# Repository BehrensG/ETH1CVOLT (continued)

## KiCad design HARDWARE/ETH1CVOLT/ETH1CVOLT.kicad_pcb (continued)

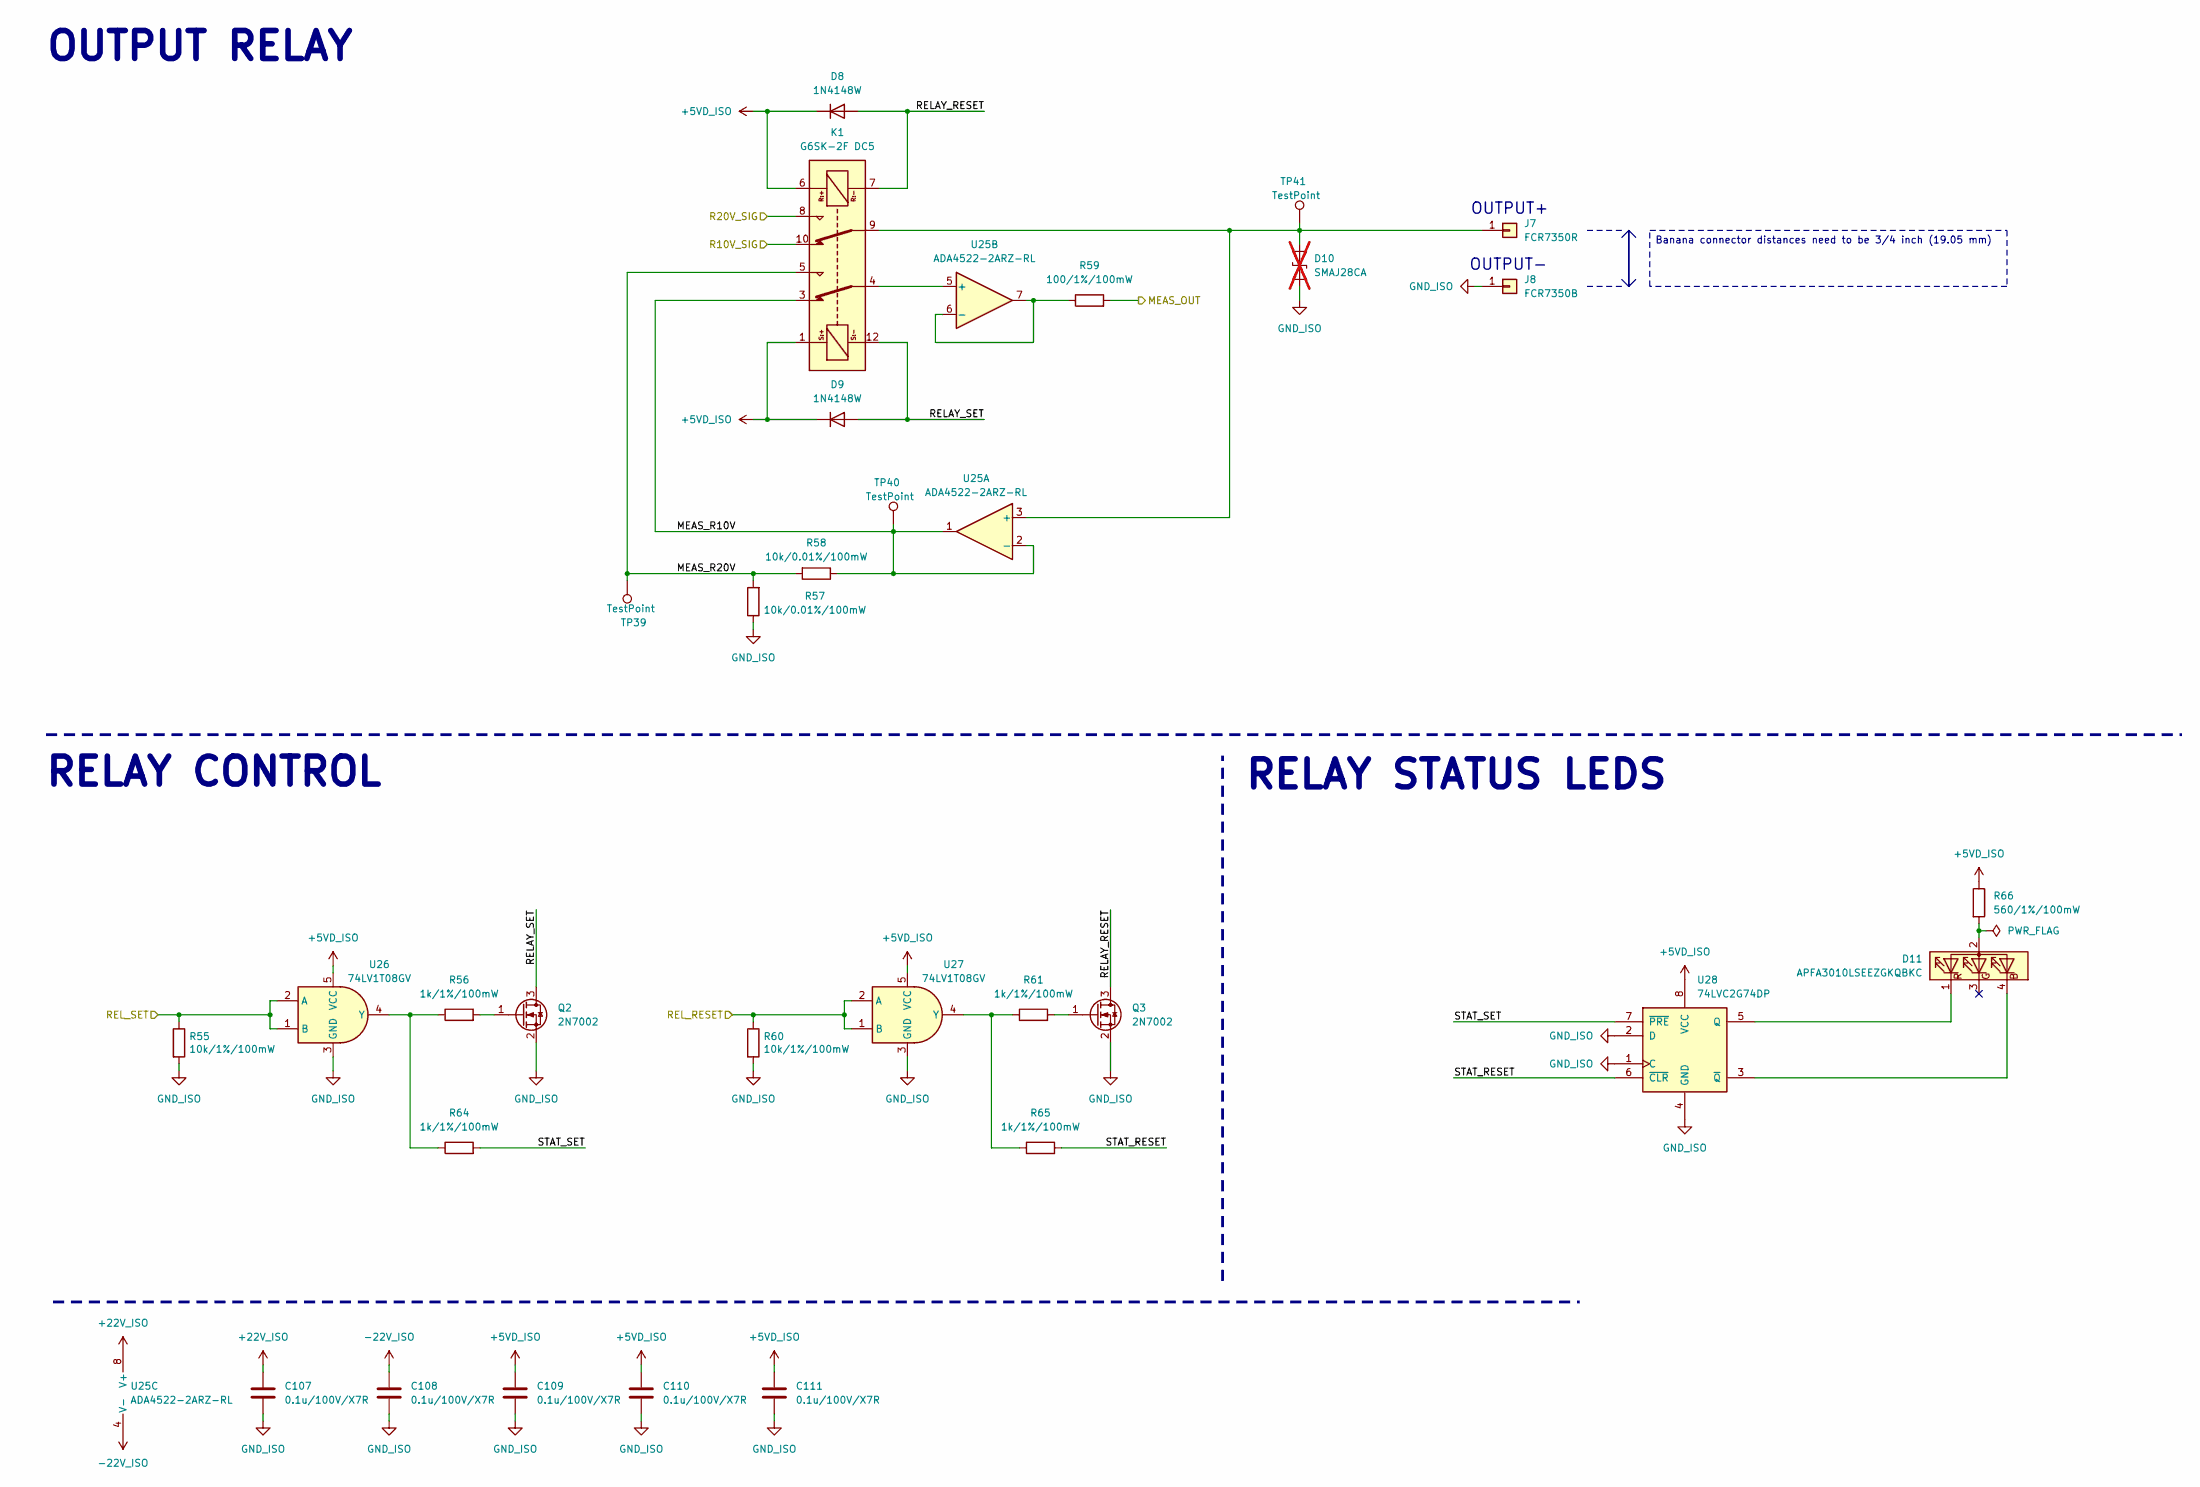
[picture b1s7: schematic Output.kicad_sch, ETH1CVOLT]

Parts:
C107, C108, C109, C110, C111: 0.1u/100V/X7R; C_0603_1608Metric_Pad1.08x0.95mm_HandSolder
D8, D9: 1N4148W; D_SOD-123
D10: SMAJ28CA; D_SMA; not fitted
D11: APFA3010LSEEZGKQBKC; LED_Kingbright_APFA3010_3x1.5mm_Horizontal
J7: FCR7350R; S16N-PC
J8: FCR7350B; S16N-PC
K1: G6SK-2F DC5; Relay_DPDT_Omron_G6SK-2F
Q2, Q3: 2N7002; SOT-23
R55, R60: 10k/1%/100mW; R_0603_1608Metric_Pad0.98x0.95mm_HandSolder
R56, R61, R64, R65: 1k/1%/100mW; R_0603_1608Metric_Pad0.98x0.95mm_HandSolder
R57, R58: 10k/0.01%/100mW; R_0603_1608Metric_Pad0.98x0.95mm_HandSolder
R59: 100/1%/100mW; R_0603_1608Metric_Pad0.98x0.95mm_HandSolder
R66: 560/1%/100mW; R_0603_1608Metric_Pad0.98x0.95mm_HandSolder
TP39, TP40, TP41: TestPoint; TestPoint_Pad_D1.5mm
U25: ADA4522-2ARZ-RL; SOIC-8_3.9x4.9mm_P1.27mm
U26, U27: 74LV1T08GV; SC-74A-5_1.55x2.9mm_P0.95mm
U28: 74LVC2G74DP; TSSOP-8_3x3mm_P0.65mm

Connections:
+5VD_ISO: C109.1, C110.1, C111.1, D8.1 (K), D9.1 (K), K1.1, K1.6, R66.1, U26.5 (VCC), U27.5 (VCC), U28.8 (VCC); also elsewhere on the board
+22V_ISO: C107.1, U25.8 (V+); also elsewhere on the board
-22V_ISO: C108.1, U25.4 (V-); also elsewhere on the board
/BLOCK DIAGRAM/ADC/MEAS_OUT: R59.2; also elsewhere on the board
/BLOCK DIAGRAM/ISO DIG/REL_RESET: R60.1, U27.1 (B), U27.2 (A); also elsewhere on the board
/BLOCK DIAGRAM/ISO DIG/REL_SET: R55.1, U26.1 (B), U26.2 (A); also elsewhere on the board
/BLOCK DIAGRAM/OUTPUT/MEAS_R10V: K1.3, R58.1, TP40.1 (1_1), U25.1, U25.2 (-)
/BLOCK DIAGRAM/OUTPUT/MEAS_R20V: K1.5, R57.2, R58.2, TP39.1 (1_1)
/BLOCK DIAGRAM/OUTPUT/R10V_SIG: K1.10; also elsewhere on the board
/BLOCK DIAGRAM/OUTPUT/R20V_SIG: K1.8; also elsewhere on the board
/BLOCK DIAGRAM/OUTPUT/RELAY_RESET: D8.2 (A), K1.7, Q3.3 (D)
/BLOCK DIAGRAM/OUTPUT/RELAY_SET: D9.2 (A), K1.12, Q2.3 (D)
/BLOCK DIAGRAM/OUTPUT/STAT_RESET: R65.2, U28.6 (~CLR)
/BLOCK DIAGRAM/OUTPUT/STAT_SET: R64.2, U28.7 (~PRE)
GND_ISO: C107.2, C108.2, C109.2, C110.2, C111.2, D10.1 (A1), J8.1 (Pin_1_1), Q2.2 (S), Q3.2 (S), R55.2, R57.1, R60.2, U26.3 (GND), U27.3 (GND), U28.1 (C), U28.2 (D), U28.4 (GND); also elsewhere on the board
unnamed: D10.2 (A2), J7.1 (Pin_1_1), K1.9, TP41.1 (1_1), U25.3 (+)
unnamed: D11.2 (A), R66.2
unnamed: D11.4 (B), U28.3 (~Q)
unnamed: D11.1 (R), U28.5 (Q)
unnamed: Q2.1 (G), R56.2
unnamed: Q3.1 (G), R61.2
unnamed: K1.4, U25.5 (+)
unnamed: R59.1, U25.6 (-), U25.7
unnamed: R56.1, R64.1, U26.4 (Y)
unnamed: R61.1, R65.1, U27.4 (Y)

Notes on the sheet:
RELAY CONTROL
OUTPUT-
OUTPUT+
OUTPUT RELAY
RELAY STATUS LEDS
Banana connector distances need to be 3/4 inch (19.05 mm)

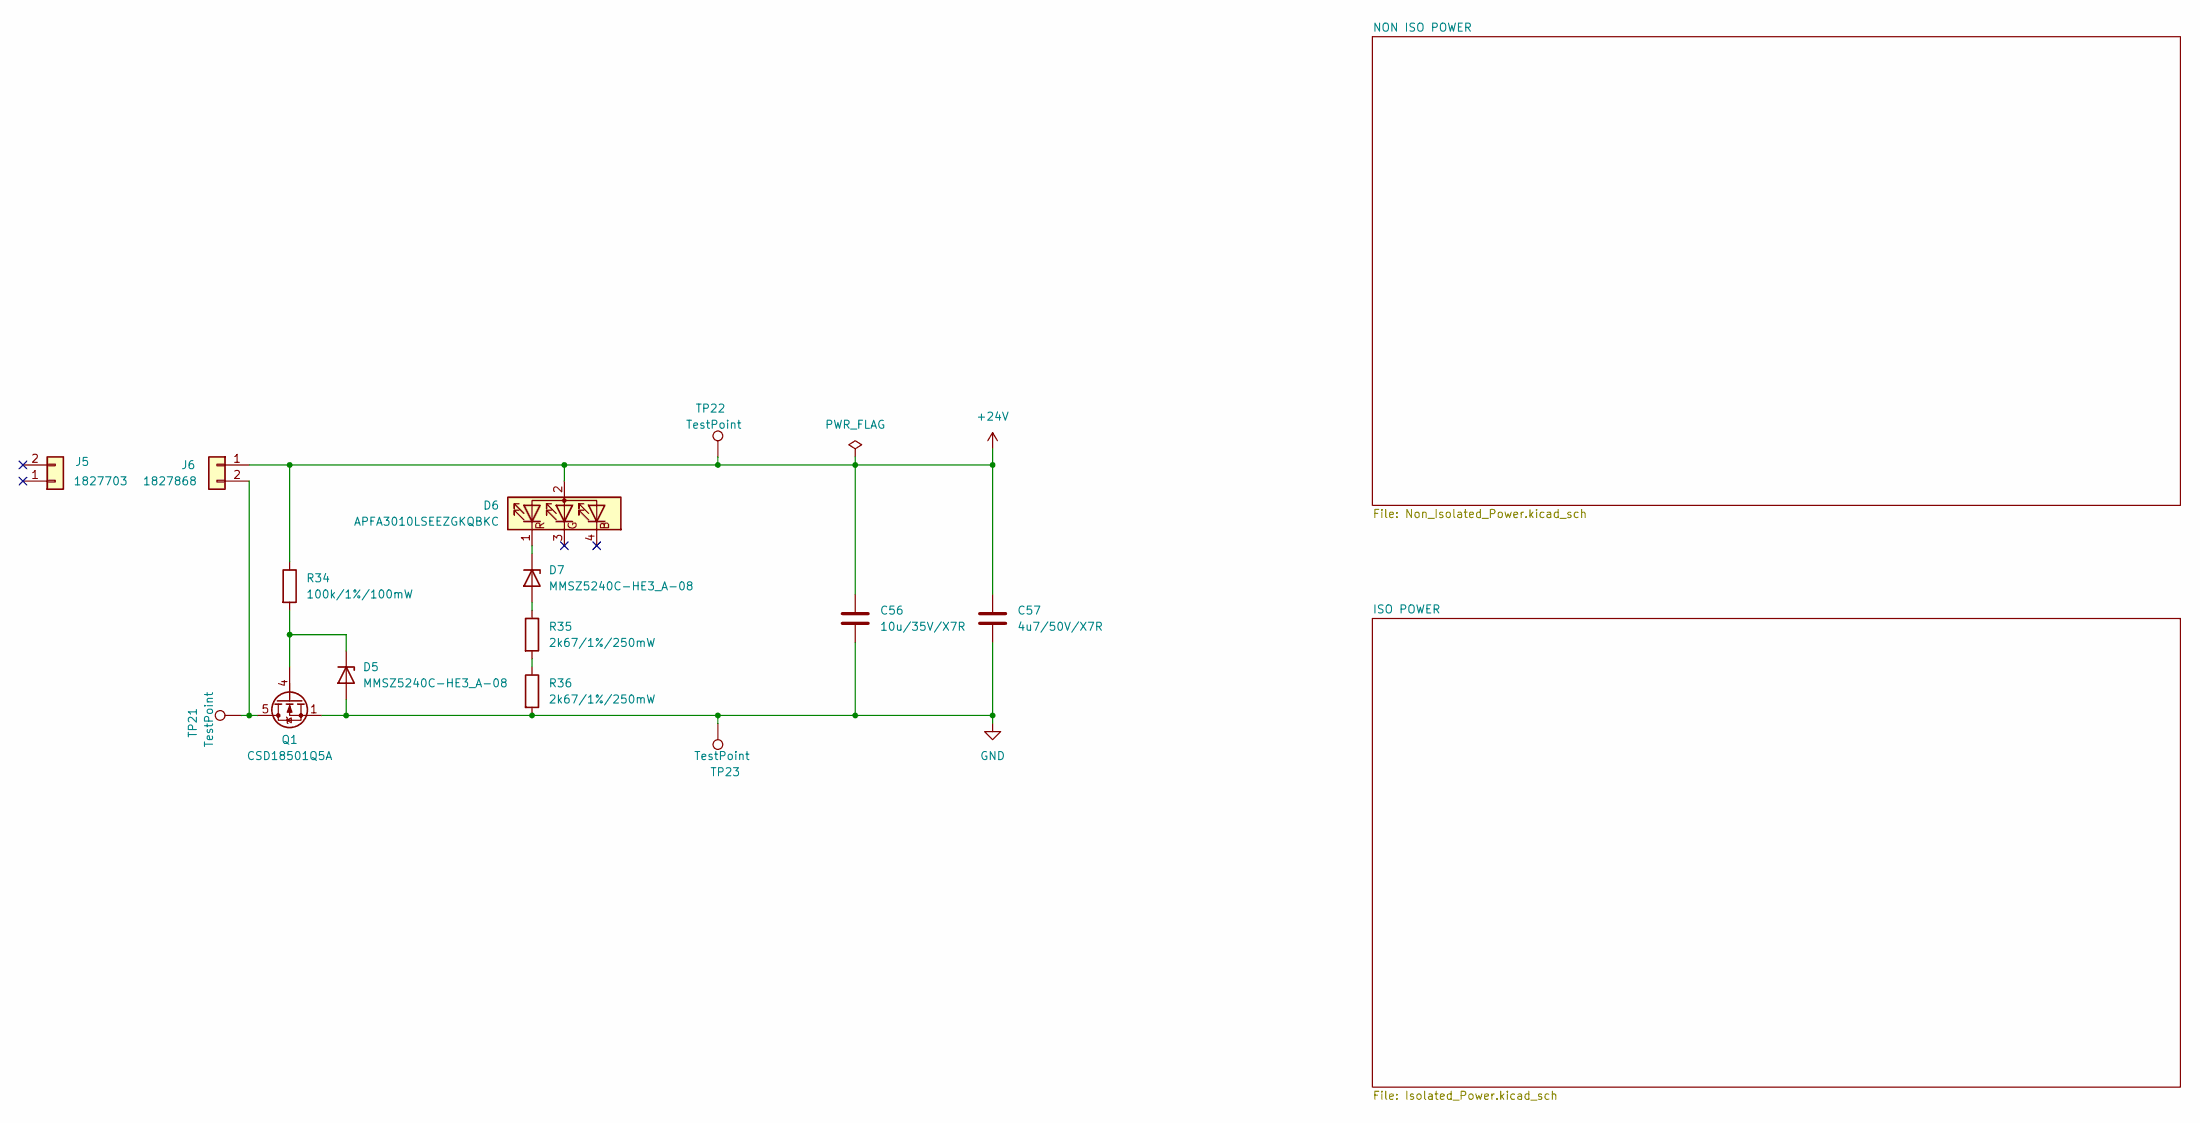
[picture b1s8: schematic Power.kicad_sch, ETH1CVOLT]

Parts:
C56: 10u/35V/X7R; C_1206_3216Metric_Pad1.33x1.80mm_HandSolder
C57: 4u7/50V/X7R; C_1206_3216Metric_Pad1.33x1.80mm_HandSolder
D5, D7: MMSZ5240C-HE3_A-08; D_SOD-123
D6: APFA3010LSEEZGKQBKC; LED_Kingbright_APFA3010_3x1.5mm_Horizontal
J5: 1827703
J6: 1827868; PhoenixContact_MC_1,5_2-GF-3.81_1x02_P3.81mm_Horizontal_Thr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
Q1: CSD18501Q5A; TDSON-8-1
R34: 100k/1%/100mW; R_0603_1608Metric_Pad0.98x0.95mm_HandSolder
R35, R36: 2k67/1%/250mW; R_0805_2012Metric_Pad1.20x1.40mm_HandSolder
TP21, TP22, TP23: TestPoint; TestPoint_Pad_D1.5mm

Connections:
+24V: C56.1, C57.1, D6.2 (A), J6.1, R34.1, TP22.1 (1_1); also elsewhere on the board
GND: C56.2, C57.2, D5.2 (A), Q1.1 (S), Q1.2 (S), Q1.3 (S), R36.2, TP23.1 (1_1); also elsewhere on the board
unnamed: D5.1 (K), Q1.4 (G), R34.2
unnamed: D6.1 (R), D7.1 (K)
unnamed: D7.2 (A), R35.1
unnamed: J6.2, Q1.5 (D), TP21.1 (1_1)
unnamed: R35.2, R36.1

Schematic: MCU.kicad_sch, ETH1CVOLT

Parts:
C1, C2, C3, C4, C5, C8, C13, C14: 0.1u/100V/X7R; C_0603_1608Metric_Pad1.08x0.95mm_HandSolder
C6, C9: 8p/100V/X7R; C_0603_1608Metric_Pad1.08x0.95mm_HandSolder
C7: 1u/16V/X7R; C_0603_1608Metric_Pad1.08x0.95mm_HandSolder
C10, C12: 2u2/16V/X7R; C_0603_1608Metric_Pad1.08x0.95mm_HandSolder
C11: 10u/16V/X7R; C_0805_2012Metric_Pad1.18x1.45mm_HandSolder
FB1: 742792031; L_0805_2012Metric_Pad1.05x1.20mm_HandSolder
J1: 20021111-00010T4LF; PinHeader_2x05_P1.27mm_Vertical
JP1: SolderJumper_2_Open; SolderJumper-2_P1.3mm_Open_Pad1.0x1.5mm
R1, R2: 10k/1%/100mW; R_0603_1608Metric_Pad0.98x0.95mm_HandSolder
R3, R4, R68, R69, R70, R73, R74, R75: 4k7/1%/100mW; R_0603_1608Metric_Pad0.98x0.95mm_HandSolder
U1: STM32H743VITx; LQFP-100_14x14mm_P0.5mm
U2: 24LC08B-E/MS; MSOP-8_3x3mm_P0.65mm
Y1: NX5032GA-16; NX5032GA

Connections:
+3.3V: C1.1, C2.1, C3.1, C4.1, C5.1, C7.1, C14.2, FB1.2, J1.1, R1.1, R2.2, R3.1, R4.1, R73.1, R74.1, R75.1, U1.6 (VBAT), U1.11 (VDD), U1.27 (VDD), U1.50 (VDD), U1.75 (VDD), U1.100 (VDD), U2.8 (VCC); also elsewhere on the board
/BLOCK DIAGRAM/ETHERNET/REF_CLK: U1.23 (PA1); also elsewhere on the board
/BLOCK DIAGRAM/ETHERNET/RMII_CRS_DV: U1.31 (PA7); also elsewhere on the board
/BLOCK DIAGRAM/ETHERNET/RMII_MDC: U1.16 (PC1); also elsewhere on the board
/BLOCK DIAGRAM/ETHERNET/RMII_MDIO: U1.24 (PA2); also elsewhere on the board
/BLOCK DIAGRAM/ETHERNET/RMII_RXD0: U1.32 (PC4); also elsewhere on the board
/BLOCK DIAGRAM/ETHERNET/RMII_RXD1: U1.33 (PC5); also elsewhere on the board
/BLOCK DIAGRAM/ETHERNET/RMII_TXD0: U1.51 (PB12); also elsewhere on the board
/BLOCK DIAGRAM/ETHERNET/RMII_TXD1: U1.52 (PB13); also elsewhere on the board
/BLOCK DIAGRAM/ETHERNET/RMII_TXEN: U1.47 (PB11); also elsewhere on the board
/BLOCK DIAGRAM/ISO DIG/MCU_ADC_SCLK: U1.89 (PB3); also elsewhere on the board
/BLOCK DIAGRAM/ISO DIG/MCU_ADC_SDO: U1.90 (PB4); also elsewhere on the board
/BLOCK DIAGRAM/ISO DIG/MCU_ADC_SW1: R70.1, U1.93 (PB7); also elsewhere on the board
/BLOCK DIAGRAM/ISO DIG/MCU_ADC_SW2: R69.1, U1.95 (PB8); also elsewhere on the board
/BLOCK DIAGRAM/ISO DIG/MCU_ADC_SW3: R68.1, U1.96 (PB9); also elsewhere on the board
/BLOCK DIAGRAM/ISO DIG/MCU_ADC_~CS: R75.2, U1.28 (PA4); also elsewhere on the board
/BLOCK DIAGRAM/ISO DIG/MCU_DAC_DIN: U1.80 (PC12); also elsewhere on the board
/BLOCK DIAGRAM/ISO DIG/MCU_DAC_SCLK: U1.78 (PC10); also elsewhere on the board
/BLOCK DIAGRAM/ISO DIG/MCU_DAC_~CS: R74.2, U1.77 (PA15); also elsewhere on the board
/BLOCK DIAGRAM/ISO DIG/MCU_DAC_~LDAC: R73.2, U1.81 (PD0); also elsewhere on the board
/BLOCK DIAGRAM/ISO DIG/MCU_REL_RESET: U1.97 (PE0); also elsewhere on the board
/BLOCK DIAGRAM/ISO DIG/MCU_REL_SET: U1.98 (PE1); also elsewhere on the board
/BLOCK DIAGRAM/MCU/EEPROM_nWP: U1.68 (PA9), U2.7 (WP)
/BLOCK DIAGRAM/MCU/I2C3_SCL: R4.2, U1.67 (PA8), U2.6 (SCL)
/BLOCK DIAGRAM/MCU/I2C3_SDA: R3.2, U1.66 (PC9), U2.5 (SDA)
/BLOCK DIAGRAM/MCU/MCU_DEF: JP1.2 (B), R2.1, U1.1 (PE2)
/BLOCK DIAGRAM/MCU/NRST: C8.1, J1.10, R1.2, U1.14 (NRST); also elsewhere on the board
/BLOCK DIAGRAM/MCU/TCK_SWCLK: J1.4, U1.76 (PA14)
/BLOCK DIAGRAM/MCU/TMS_SWDIO: J1.2, U1.72 (PA13)
GND: C1.2, C2.2, C3.2, C4.2, C5.2, C6.2, C7.2, C8.2, C9.2, C10.2, C11.2, C12.2, C13.2, C14.1, J1.3, J1.5, JP1.1 (A), R68.2, R69.2, R70.2, U1.10 (VSS), U1.19 (VSSA), U1.26 (VSS), U1.49 (VSS), U1.74 (VSS), U1.94 (BOOT0), U1.99 (VSS), U2.1 (A0), U2.2 (A1), U2.3 (A2), U2.4 (GND); also elsewhere on the board
unnamed: C10.1, U1.48 (VCAP)
unnamed: C12.1, U1.73 (VCAP)
unnamed: C6.1, U1.12 (PH0), Y1.1
unnamed: C9.1, U1.13 (PH1), Y1.2
VDDA: C11.1, C13.1, FB1.1, U1.20 (VREF+), U1.21 (VDDA)

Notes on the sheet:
MCU
EEPROM
Connect to VBAT
PROGRAMMING INTERFACE

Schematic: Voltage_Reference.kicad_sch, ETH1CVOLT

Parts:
C35, C36, C37, C40, C42: 0.1u/100V/X7R; C_0603_1608Metric_Pad1.08x0.95mm_HandSolder
C38, C41, C43: 1u/16V/X7R; C_0603_1608Metric_Pad1.08x0.95mm_HandSolder
C39: 10u/35V/X7R; C_1206_3216Metric_Pad1.33x1.80mm_HandSolder
J3, J4: TSW-102-23-G-S; PinHeader_1x02_P2.54mm_Vertical
R18: 0R/5%/100mW; R_0603_1608Metric_Pad0.98x0.95mm_HandSolder; not fitted
R19: 100/1%/100mW; R_0603_1608Metric_Pad0.98x0.95mm_HandSolder
TP5: TestPoint; TestPoint_Pad_D1.5mm
U7: ADR4550CRZ; SOIC-8_3.9x4.9mm_P1.27mm
U8: ADA4522-1ARZ; SOIC-8_3.9x4.9mm_P1.27mm

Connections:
+5VREF_ISO: C42.1, C43.1, J4.1, R19.1, TP5.1 (1_1); also elsewhere on the board
+14V_ISO: C35.1, C37.1, C38.1, C39.1, U7.2 (IN), U8.7 (V+); also elsewhere on the board
-14V_ISO: C36.1, U8.4 (V-); also elsewhere on the board
GND_ISO: C35.2, C36.2, C37.2, C38.2, C39.2, C40.2, C41.2, C42.2, C43.2, J3.2, J4.2, U7.4 (GND); also elsewhere on the board
unnamed: C40.1, C41.1, J3.1, R18.1, U7.6 (OUT), U8.3 (+)
unnamed: R18.2, R19.2, U8.2 (-), U8.6

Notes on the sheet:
Optional MAX6350

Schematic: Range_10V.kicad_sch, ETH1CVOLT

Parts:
C52, C53: 0.1u/100V/X7R; C_0603_1608Metric_Pad1.08x0.95mm_HandSolder
D3: BAV199; SOT-23
R28, R29: 10k/0.01%/100mW; R_0603_1608Metric_Pad0.98x0.95mm_HandSolder
TP19: TestPoint; TestPoint_Pad_D1.5mm
U13: ADA4522-1ARZ; SOIC-8_3.9x4.9mm_P1.27mm

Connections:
+14V_ISO: C52.1, D3.2 (A), U13.7 (V+); also elsewhere on the board
-14V_ISO: C53.1, D3.1 (K), U13.4 (V-); also elsewhere on the board
/BLOCK DIAGRAM/DAC/DAC_SIG: U13.3 (+); also elsewhere on the board
/BLOCK DIAGRAM/OUTPUT/R10V_SIG: D3.3 (K), R29.2, TP19.1 (1_1), U13.6; also elsewhere on the board
GND_ISO: C52.2, C53.2, R28.1; also elsewhere on the board
unnamed: R28.2, R29.1, U13.2 (-)

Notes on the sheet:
+/- 10V

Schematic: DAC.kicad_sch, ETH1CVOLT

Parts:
C44, C45, C46, C47: 0.1u/100V/X7R; C_0603_1608Metric_Pad1.08x0.95mm_HandSolder
R20, R21, R22, R23: 0R/5%/100mW; R_0603_1608Metric_Pad0.98x0.95mm_HandSolder
R24, R25, R26, R27: 0R/5%/100mW; R_0603_1608Metric_Pad0.98x0.95mm_HandSolder; not fitted
R63: 4k7/1%/100mW; R_0603_1608Metric_Pad0.98x0.95mm_HandSolder
TP6: TestPoint; TestPoint_Pad_D1.5mm
U9: MAX5719GSD+; SOIC-14_3.9x8.7mm_P1.27mm
U10: ADA4522-1ARZ; SOIC-8_3.9x4.9mm_P1.27mm

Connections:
+5VD_ISO: C44.1, R63.1, U9.14 (VDD); also elsewhere on the board
+5VREF_ISO: C45.1, U9.5 (REFS), U9.6 (REFF); also elsewhere on the board
+7V_ISO: R22.2; also elsewhere on the board
+14V_ISO: R25.2; also elsewhere on the board
-7V_ISO: R23.1; also elsewhere on the board
-14V_ISO: R26.1; also elsewhere on the board
/BLOCK DIAGRAM/DAC/DAC_DIN: U9.10 (DIN); also elsewhere on the board
/BLOCK DIAGRAM/DAC/DAC_SCLK: U9.8 (SCLK); also elsewhere on the board
/BLOCK DIAGRAM/DAC/DAC_SIG: R20.2, R24.2, TP6.1 (1_1), U10.6; also elsewhere on the board
/BLOCK DIAGRAM/DAC/DAC_~CS: U9.7 (~CS); also elsewhere on the board
/BLOCK DIAGRAM/DAC/DAC_~LDAC: R63.2, U9.11 (~LDAC); also elsewhere on the board
GND_ISO: C44.2, C45.2, C46.1, C47.1, R27.1, U9.3 (AGNDF), U9.4 (AGNDS), U9.12 (DGND); also elsewhere on the board
unnamed: R21.1, U9.13 (INV)
unnamed: R20.1, U9.1 (RFB)
unnamed: U9.2 (OUT), U10.3 (+)
unnamed: R21.2, R24.1, U10.2 (-)
unnamed: C46.2, R22.1, R25.1, U10.7 (V+)
unnamed: C47.2, R23.2, R26.2, R27.2, U10.4 (V-)

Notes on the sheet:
+/- 5V

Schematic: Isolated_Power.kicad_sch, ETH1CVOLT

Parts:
C58, C59, C60, C61, C67, C68, C69, C70, C71, C82, C83, C87, C88, C97, C98, C99, C100, C101, C102: 10u/35V/X7R; C_1206_3216Metric_Pad1.33x1.80mm_HandSolder
C62, C63, C64, C65, C66, C72, C73, C74, C75, C76, C78, C79, C80, C84, C85, C91, C92, C93, C94, C95, C96: 4u7/50V/X7R; C_1206_3216Metric_Pad1.33x1.80mm_HandSolder
C77, C81, C86, C89, C90: C; C_0603_1608Metric_Pad1.08x0.95mm_HandSolder; not fitted
L1: RLS-226
L2, L3: 78438366047
R37: 12k/1%/100mW; R_0603_1608Metric_Pad0.98x0.95mm_HandSolder
R38: 140k/1%/100mW; R_0603_1608Metric_Pad0.98x0.95mm_HandSolder
R39: 160k/1%/100mW; R_0603_1608Metric_Pad0.98x0.95mm_HandSolder
R40: 15k/1%/100mW; R_0603_1608Metric_Pad0.98x0.95mm_HandSolder
R41, R45, R49, R50: 10k/1%/100mW; R_0603_1608Metric_Pad0.98x0.95mm_HandSolder
R42: 187k/1%/100mW; R_0603_1608Metric_Pad0.98x0.95mm_HandSolder
R43: 182k/1%/100mW; R_0603_1608Metric_Pad0.98x0.95mm_HandSolder
R44, R48, R53, R54: 560/1%/100mW; R_0603_1608Metric_Pad0.98x0.95mm_HandSolder
R46: 18k/1%/100mW; R_0603_1608Metric_Pad0.98x0.95mm_HandSolder
R47: 105k/1%/100mW; R_0603_1608Metric_Pad0.98x0.95mm_HandSolder
R51: 107k/1%/100mW; R_0603_1608Metric_Pad0.98x0.95mm_HandSolder
R52: 22k1/1%/100mW; R_0603_1608Metric_Pad0.98x0.95mm_HandSolder
TP24, TP25, TP26, TP27, TP28, TP29, TP30, TP31, TP32, TP33, TP34, TP35, TP36, TP37, TP42, TP43: TestPoint; TestPoint_Pad_D1.5mm
U15: RP-2424D; RP-xxxxD
U16: TMR4-2423WI; Converter_DCDC_TRACO_TMR4-xxxxWI_THT
U17: TEC2-2419WI; Converter_DCDC_TRACO_TEC2-12xxWI_24xxWI_48xxWI_THT
U18: TSR0.5-2465; Converter_DCDC_TRACO_TSR0.5-24xx_TSR0.5-24xxx_THT
U19, U20, U21: TPS7A3901DSCR; Texas_S-PVSON-N10_ThermalVias
U22, U23: ADP7142ARDZ-5.0; SOIC-8-1EP_3.9x4.9mm_P1.27mm_EP2.29x3mm

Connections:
+5VA_ISO: C93.1, C101.1, R53.2, TP35.1 (1_1), U22.1 (VOUT), U22.2 (VOUT); also elsewhere on the board
+5VD_ISO: C94.1, C102.1, R54.2, TP36.1 (1_1), U23.1 (VOUT), U23.2 (VOUT); also elsewhere on the board
+6V5_ISO: C78.1, C84.1, C85.1, C87.1, C88.1, TP43.1 (1_1), U18.3 (Vout), U22.5 (EN), U22.7 (VIN), U22.8 (VIN), U23.5 (EN), U23.7 (VIN), U23.8 (VIN)
+7V_ISO: C95.1, C99.1, R51.1, TP37.1 (1_1), U21.10 (OUTP); also elsewhere on the board
+14V_ISO: C79.1, C82.1, R39.1, TP28.1 (1_1), U19.10 (OUTP); also elsewhere on the board
+15V_ISO: C69.1, C74.1, TP26.1 (1_1), U16.6 (+Vout), U19.1 (INP), U19.2 (EN), U21.1 (INP), U21.2 (EN)
+22V_ISO: C91.1, C97.1, R43.1, TP33.1 (1_1), U20.10 (OUTP); also elsewhere on the board
+24V: C58.1, C59.1, C60.1, C62.1, C63.1, L1.1, L2.1, L3.1; also elsewhere on the board
+24V_ISO: C67.1, C72.1, TP24.1 (1_1), U15.7 (+Vout), U20.1 (INP), U20.2 (EN)
-7V_ISO: C96.2, C100.2, R47.2, TP34.1 (1_1), U21.6 (OUTN); also elsewhere on the board
-14V_ISO: C80.2, C83.2, R38.2, TP29.1 (1_1), U19.6 (OUTN); also elsewhere on the board
-15V_ISO: C70.2, C75.2, TP27.1 (1_1), U16.8 (-Vout), U19.5 (INN), U21.5 (INN)
-22V_ISO: C92.2, C98.2, R42.2, TP30.1 (1_1), U20.6 (OUTN); also elsewhere on the board
-24V_ISO: C68.2, C73.2, TP25.1 (1_1), U15.5 (-Vout), U20.5 (INN)
GND: C58.2, C59.2, C60.2, C61.2, C62.2, C63.2, C64.2, C65.2, C66.2, U15.2 (-Vin), U16.1 (-Vin), U17.1 (-Vin); also elsewhere on the board
GND_ISO: C67.2, C68.1, C69.2, C70.1, C71.2, C72.2, C73.1, C74.2, C75.1, C76.2, C77.2, C78.2, C79.2, C80.1, C81.2, C82.2, C83.1, C84.2, C85.2, C86.2, C87.2, C88.2, C89.2, C90.2, C91.2, C92.1, C93.2, C94.2, C95.2, C96.1, C97.2, C98.1, C99.2, C100.1, C101.2, C102.2, R40.2, R45.2, R49.2, R50.2, R52.2, TP31.1 (1_1), TP32.1 (1_1), U15.6 (Com), U16.7 (Com), U17.7 (-Vout), U18.2 (GND), U19.4 (GND), U19.11 (GND), U20.4 (GND), U20.11 (GND), U21.4 (GND), U21.11 (GND), U22.4 (GND), U22.9 (GND), U23.4 (GND), U23.9 (GND); also elsewhere on the board
unnamed: R44.1, R45.1, R48.1
unnamed: C61.1, C64.1, L1.2, U15.1 (+Vin)
unnamed: C65.1, L2.2, U16.2 (+Vin)
unnamed: C66.1, L3.2, U17.2 (+Vin)
unnamed: C71.1, C76.1, TP42.1 (1_1), U17.6 (+Vout), U18.1 (Vin)
unnamed: R37.1, U19.8 (BUF)
unnamed: R37.2, R38.1, U19.7 (FBN)
unnamed: R39.2, R40.1, U19.9 (FBP)
unnamed: C77.1, U19.3 (NR/SS)
unnamed: R41.1, U20.8 (BUF)
unnamed: R41.2, R42.1, U20.7 (FBN)
unnamed: R43.2, R44.2, R48.2, U20.9 (FBP)
unnamed: C81.1, U20.3 (NR/SS)
unnamed: R46.1, U21.8 (BUF)
unnamed: R46.2, R47.1, U21.7 (FBN)
unnamed: R51.2, R52.1, U21.9 (FBP)
unnamed: C86.1, U21.3 (NR/SS)
unnamed: R49.1, R53.1, U22.3 (SENSE/ADJ)
unnamed: C89.1, U22.6 (SS)
unnamed: R50.1, R54.1, U23.3 (SENSE/ADJ)
unnamed: C90.1, U23.6 (SS)

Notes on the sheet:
-7V/100mA
+6V5/500mA
+22V/100mA
-24V/21mA
+24V/21mA
+15V/133mA
+9V/222mA
-14V/100mA
-22V/100mA
+14V/100mA
+5V28/200mA
-15V/133mA
+7V/100mA

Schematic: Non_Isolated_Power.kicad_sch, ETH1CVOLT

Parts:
C103, C106: 10u/35V/X7R; C_1206_3216Metric_Pad1.33x1.80mm_HandSolder
C104, C105: 4u7/50V/X7R; C_1206_3216Metric_Pad1.33x1.80mm_HandSolder
L4: 78438366047
TP38: TestPoint; TestPoint_Pad_D1.5mm
U24: TSR0.5-2433; Converter_DCDC_TRACO_TSR0.5-24xx_TSR0.5-24xxx_THT

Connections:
+3.3V: C106.1, TP38.1 (1_1), U24.3 (Vout); also elsewhere on the board
+24V: C103.1, C104.1, L4.1; also elsewhere on the board
GND: C103.2, C104.2, C105.2, C106.2, U24.2 (GND); also elsewhere on the board
unnamed: C105.1, L4.2, U24.1 (Vin)

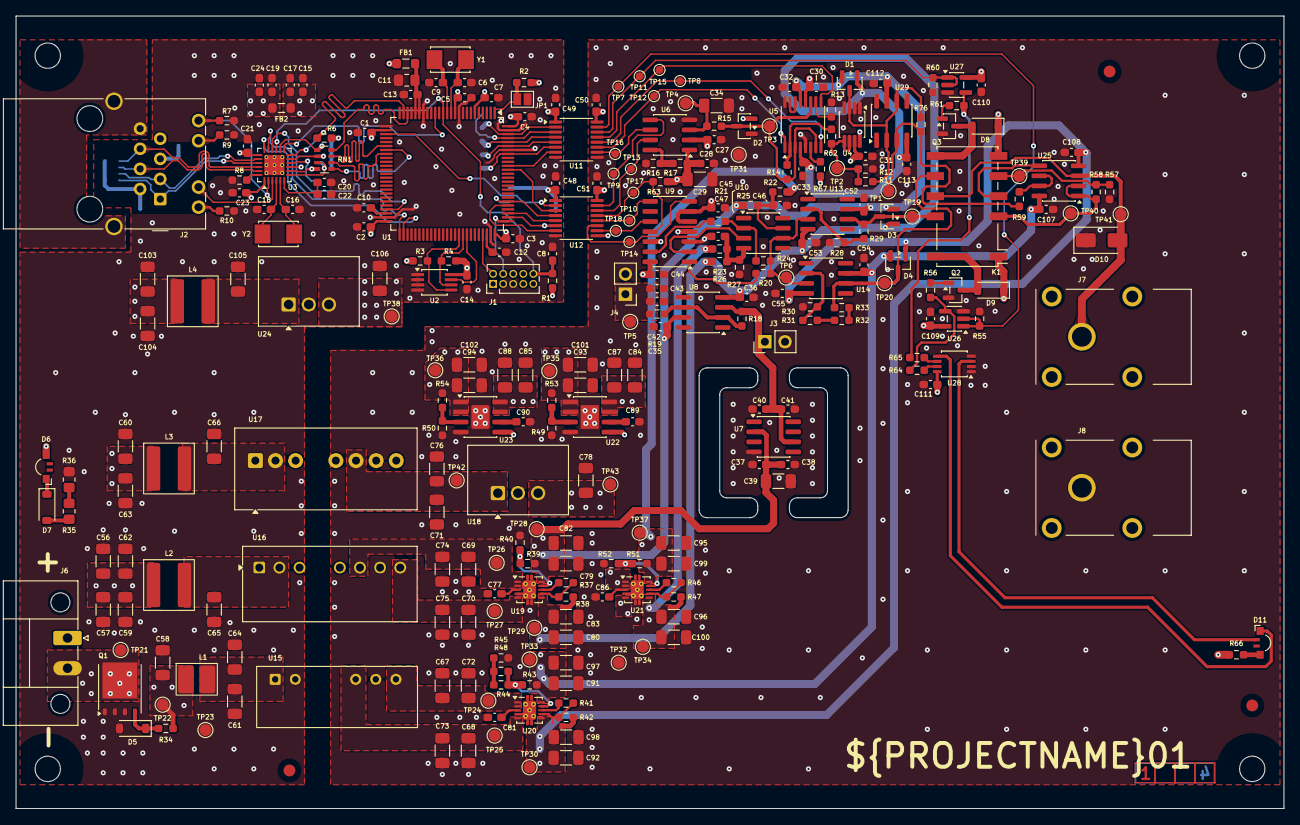
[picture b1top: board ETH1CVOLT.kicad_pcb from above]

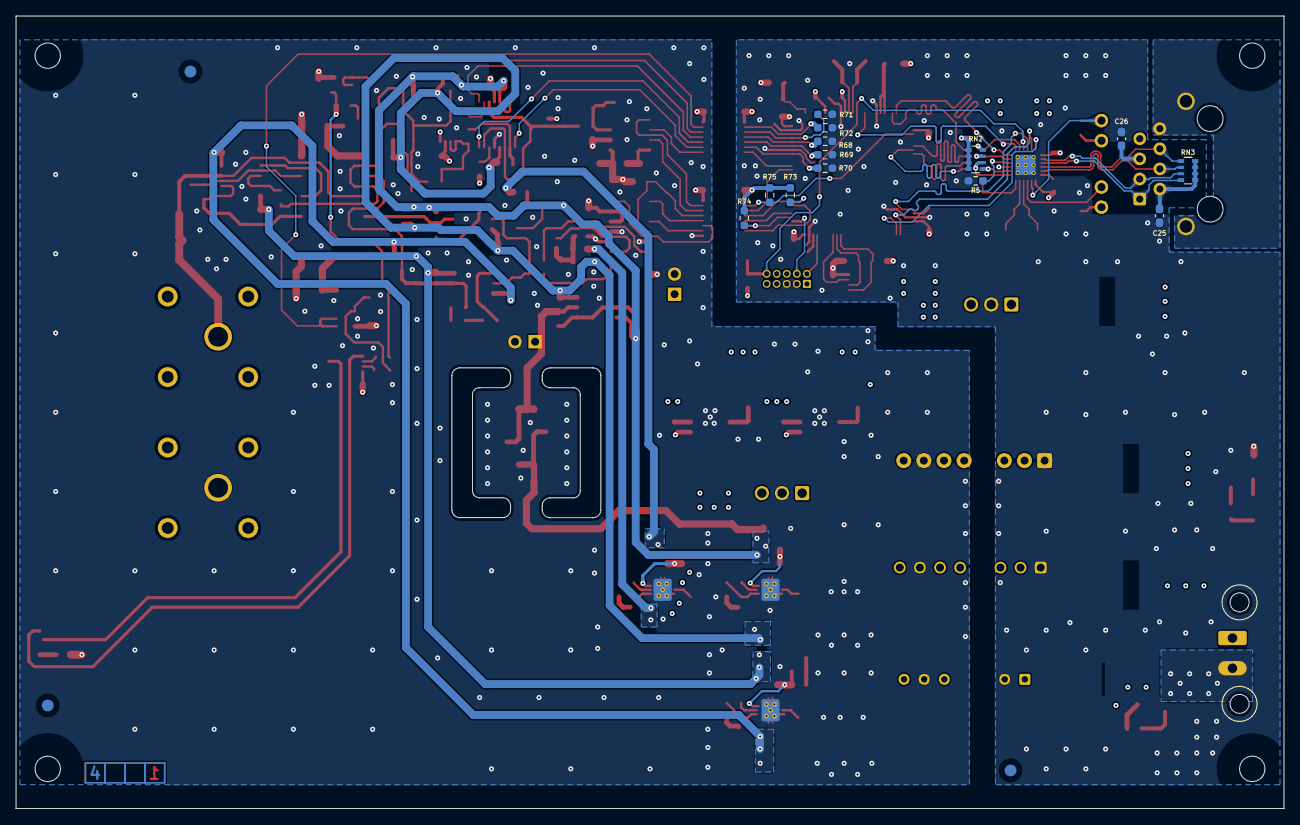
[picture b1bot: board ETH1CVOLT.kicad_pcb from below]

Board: 4 copper layers, 160.0 x 100.0 mm, 305 parts (16 on the bottom side), 150 nets.

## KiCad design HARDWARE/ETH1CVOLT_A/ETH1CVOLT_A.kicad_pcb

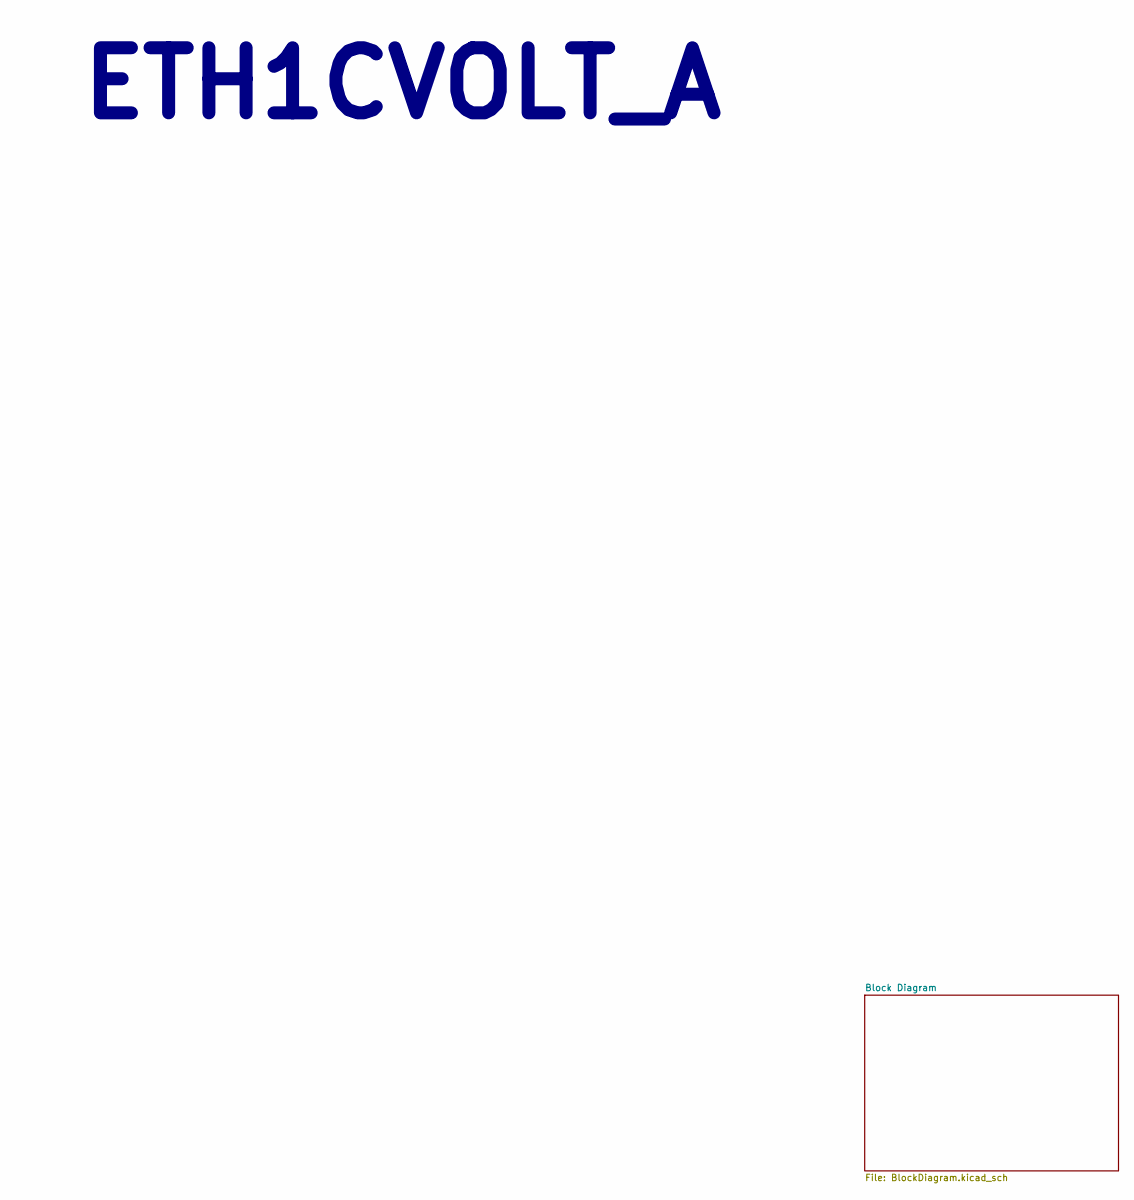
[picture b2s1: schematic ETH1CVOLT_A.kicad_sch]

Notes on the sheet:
ETH1CVOLT_A

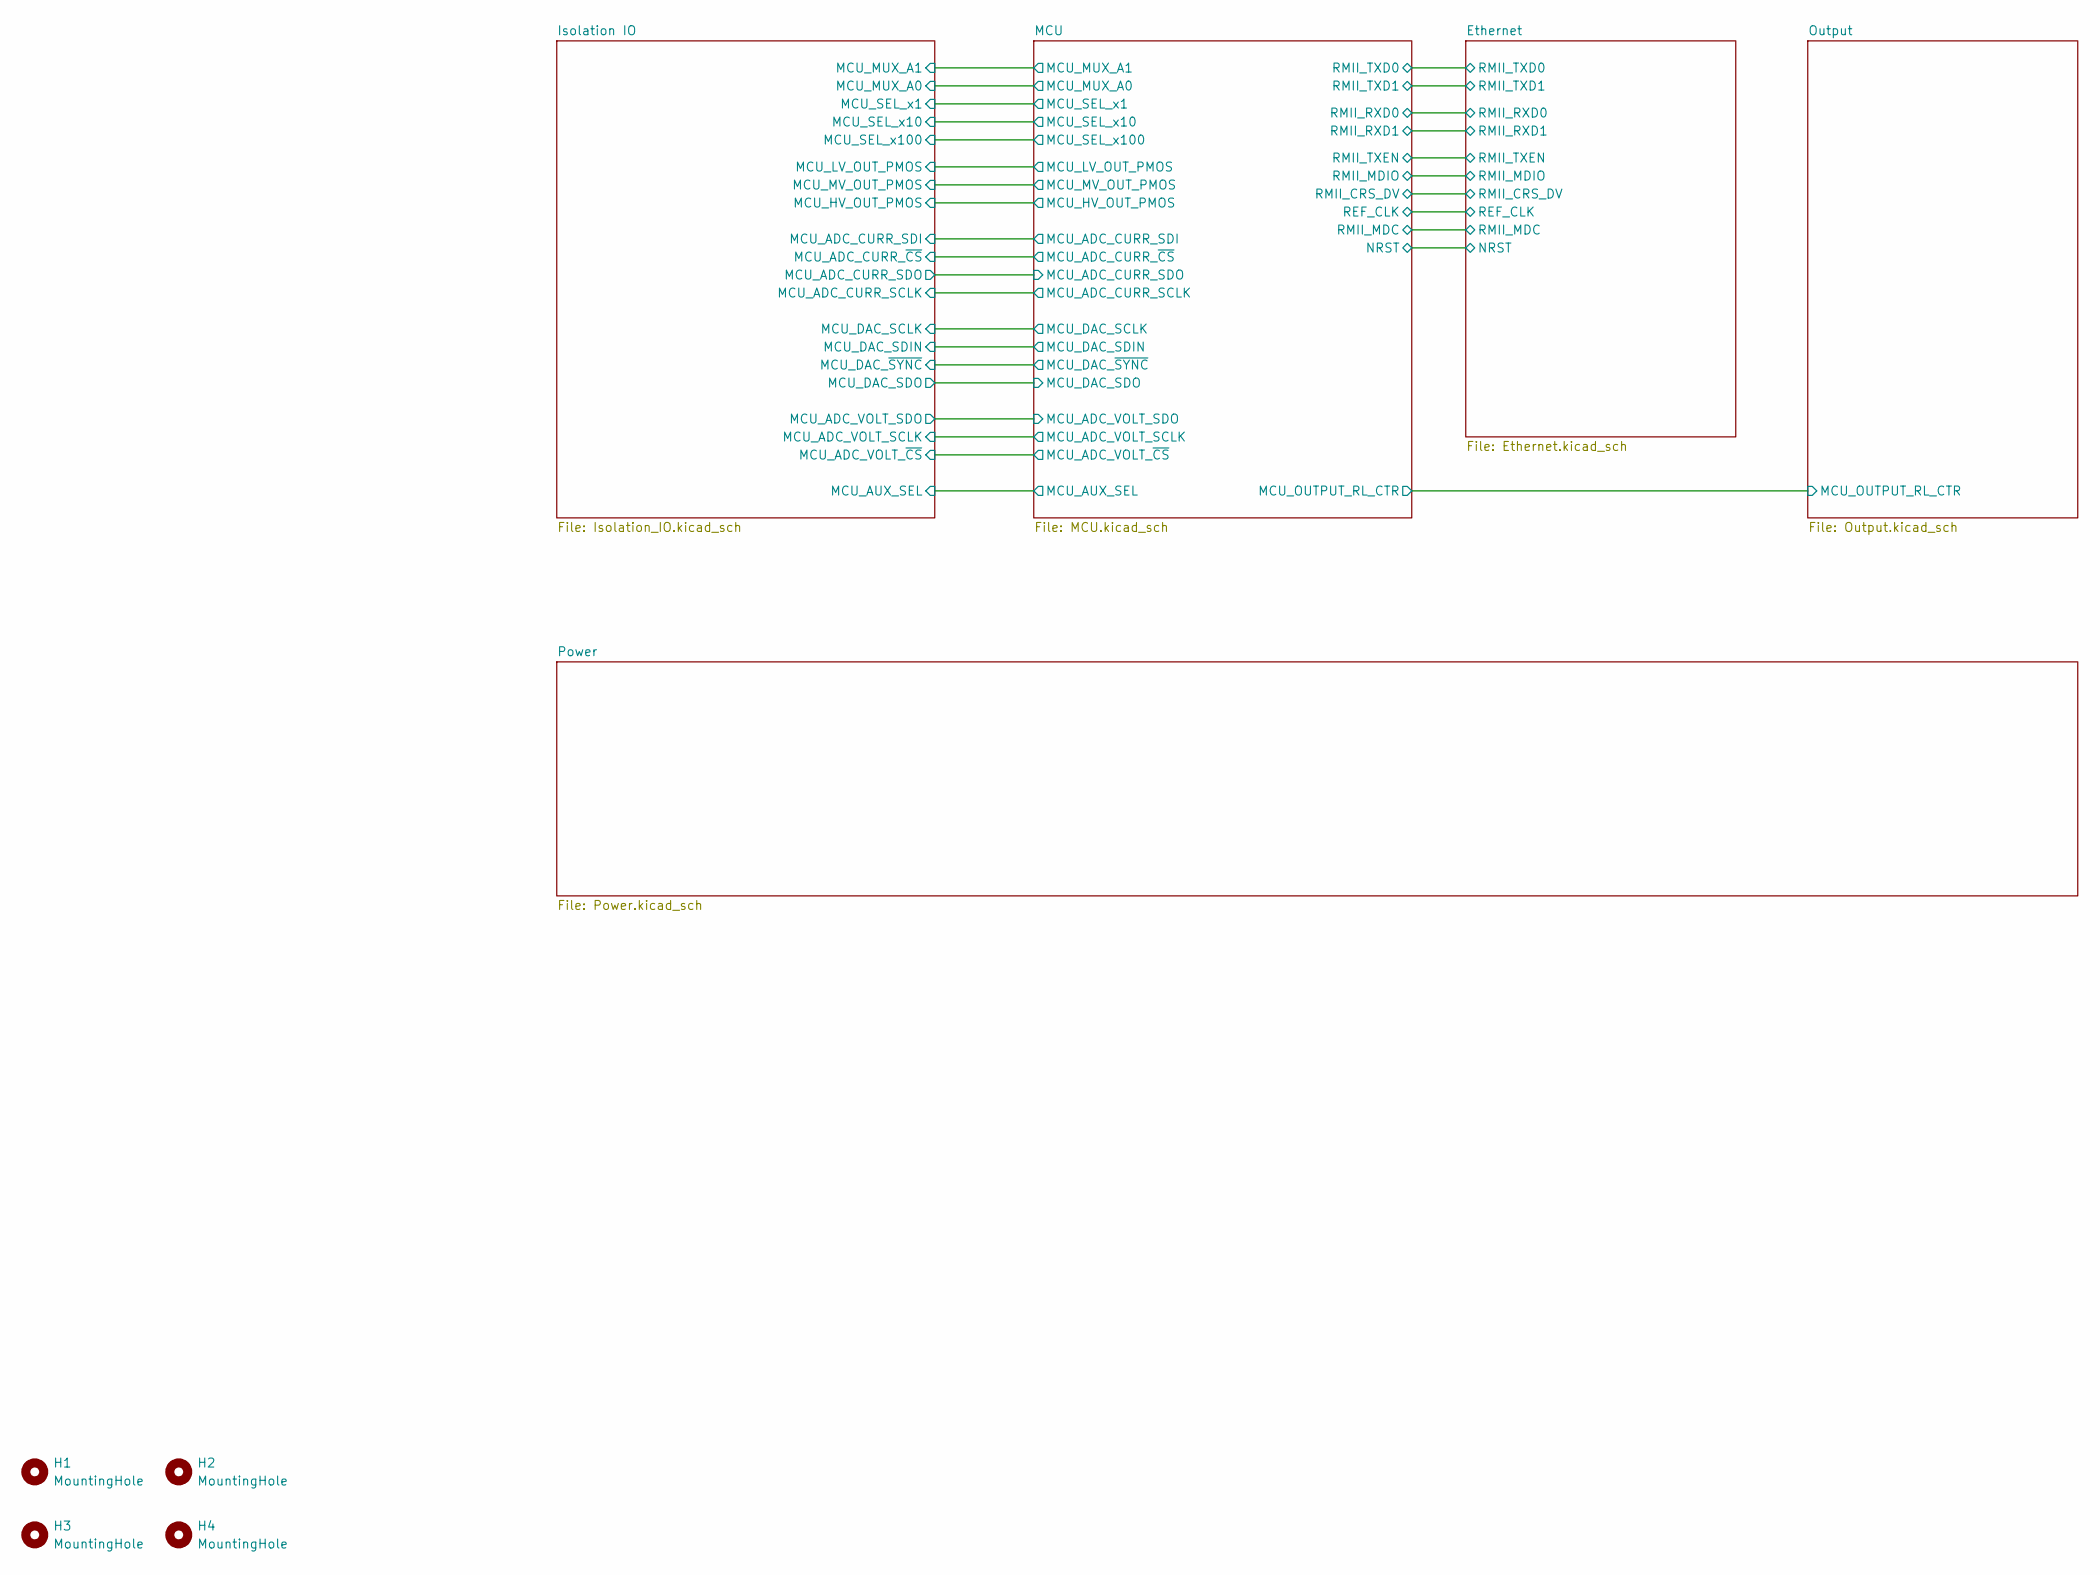
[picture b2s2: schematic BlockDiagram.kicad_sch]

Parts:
H1, H2, H3, H4: MountingHole; MountingHole_3.2mm_M3_DIN965_Pad_TopBottom
